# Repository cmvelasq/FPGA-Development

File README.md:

# QuickFeather Development Board 
- Features the PCB layout design updated with the EOS3FLF512-PDN64 BGA64 package
- Software tool : KiCad PCB Editor Ver 6.0.7  | https://www.kicad.org/
- Based on original PCB Design provided by Quicklogic | https://www.quicklogic.com/products/eos-s3/quickfeather-development-kit/

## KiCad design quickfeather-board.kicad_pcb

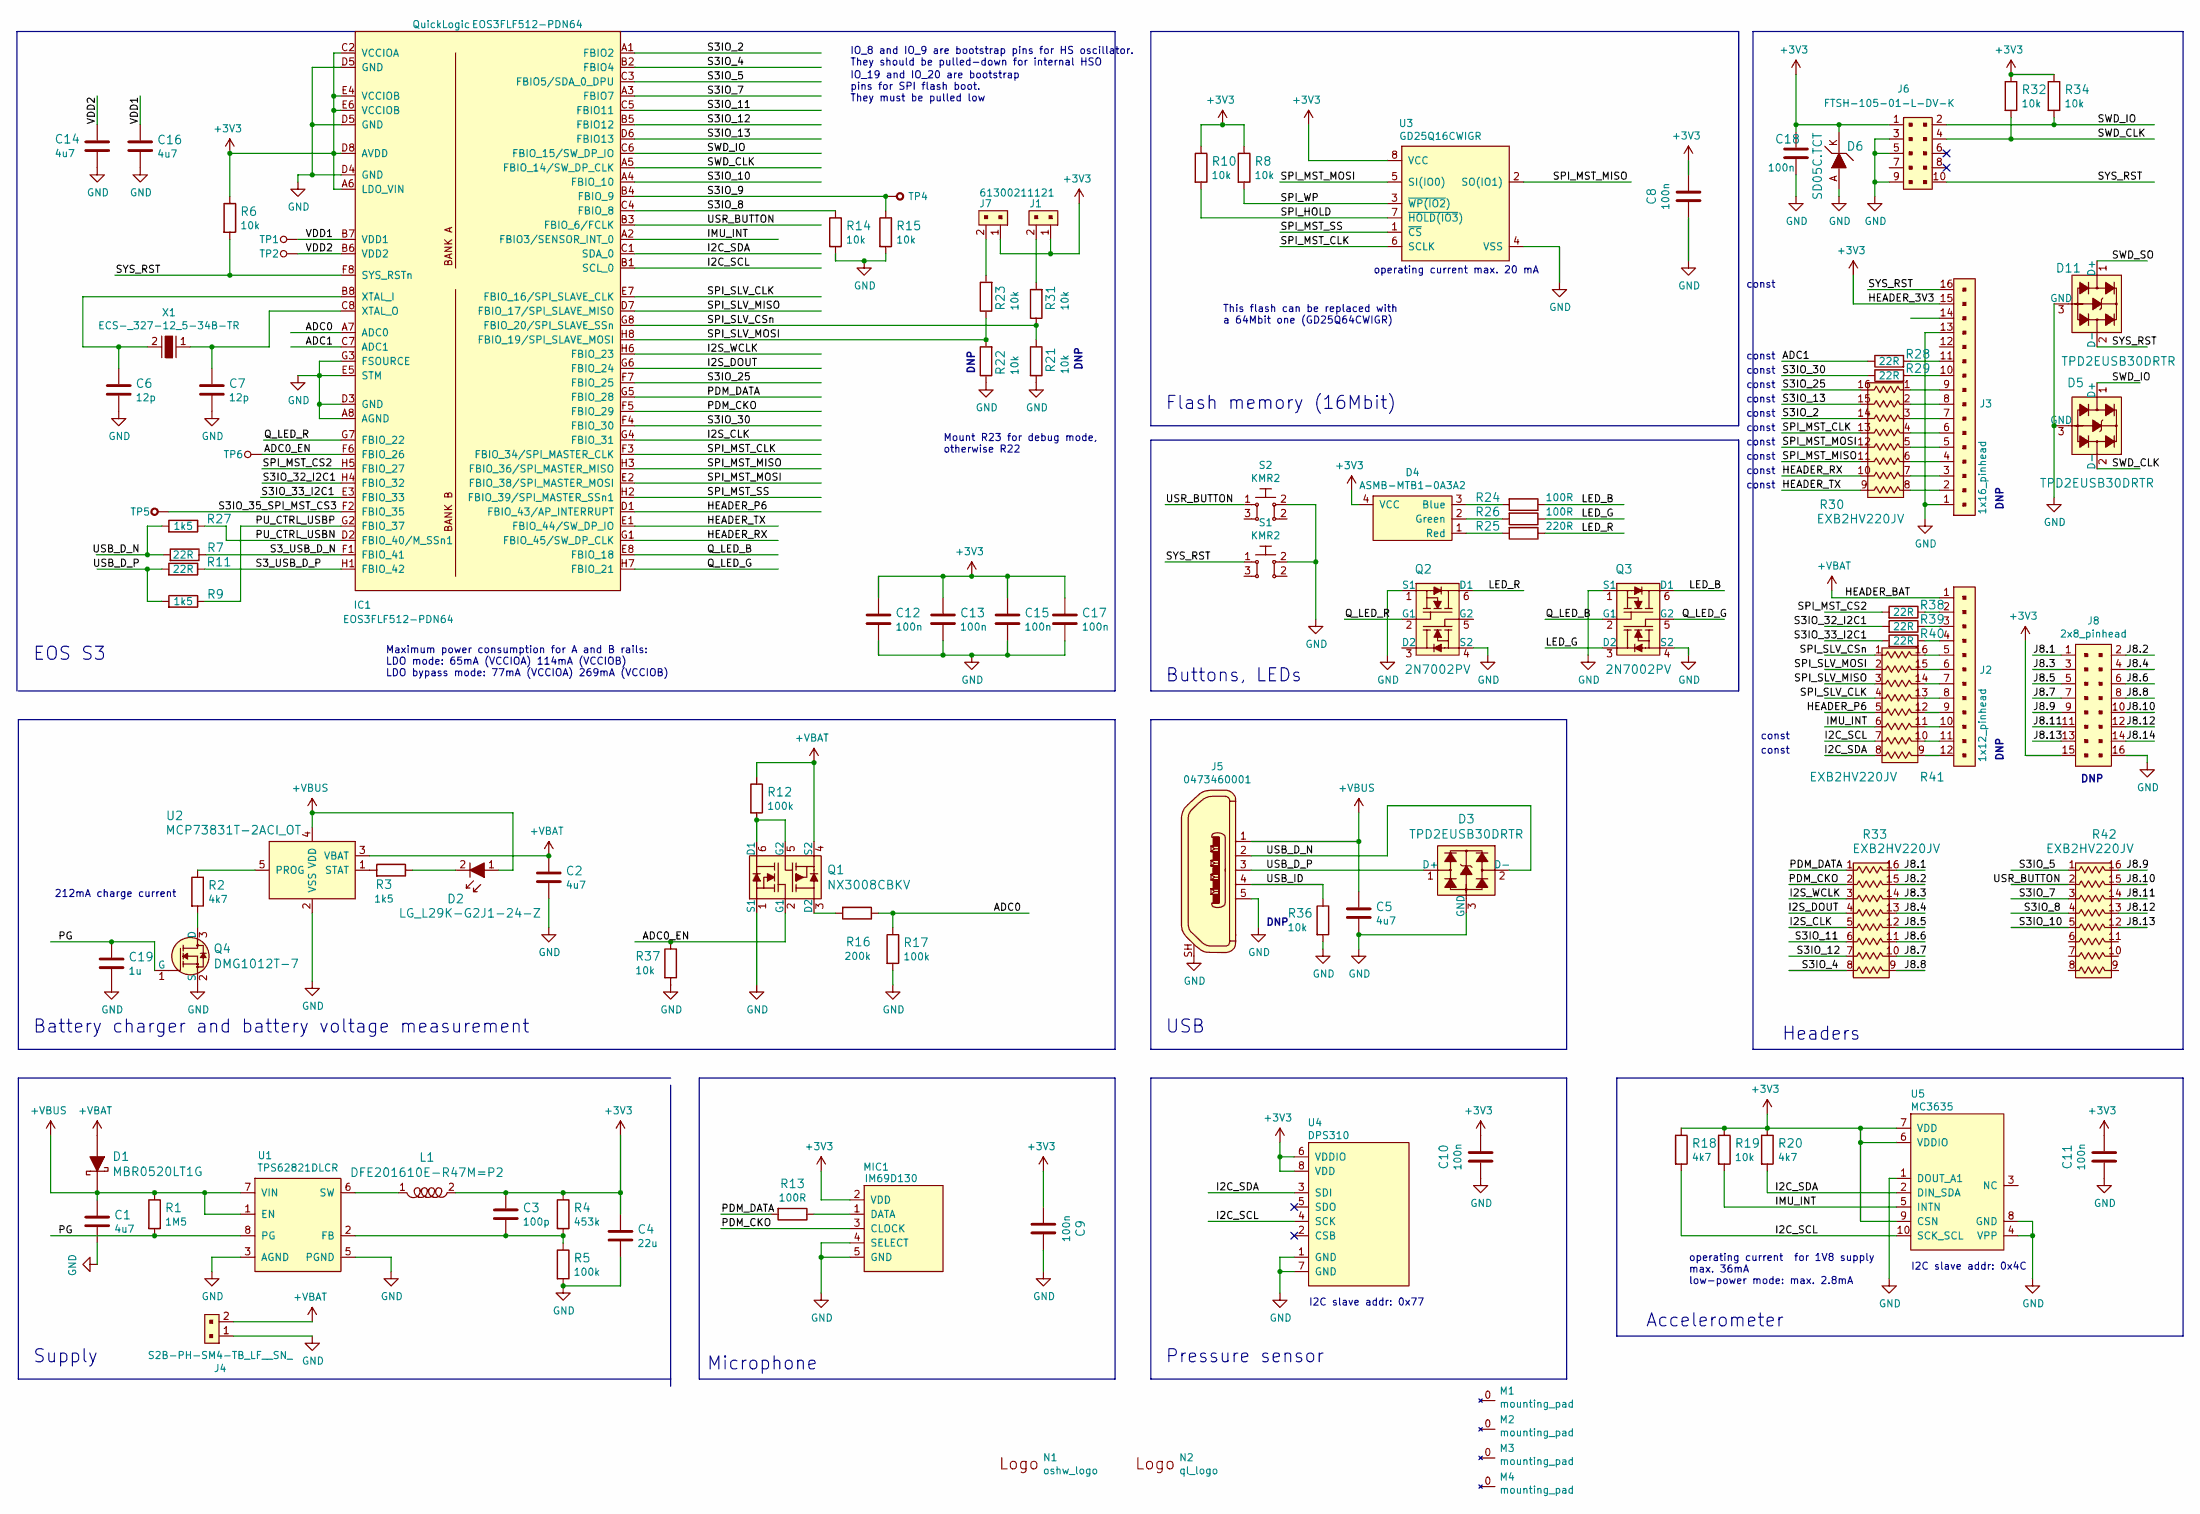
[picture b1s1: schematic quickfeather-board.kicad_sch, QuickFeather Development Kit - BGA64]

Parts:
C1, C2, C5, C14, C16: C_4u7_0603; 0603-cap; MPN C1608X5R1V475M080AC
C3: C_100p_0402; 0402-cap; MPN 0402N101J500CT
C4: C_22u_0603; 0603-cap; MPN GRM188R60J226MEA0D
C6, C7: C_12p_0402; 0402-cap; MPN CGA2B2C0G1H120J050BA
C8, C9, C10, C11, C12, C13, C15, C17, C18: C_100n_0402_6V3; 0402-cap; MPN 0402X104K6R3CT
C19: C_1u_0402; 0402-cap; MPN C1005X6S1A105K050BC
D1: MBR0520LT1G; SOD-123; MPN MBR0520LT1G
D2: LG_L29K-G2J1-24-Z; LED_0603; MPN LG L29K-G2J1-24-Z
D3, D5, D11: TPD2EUSB30DRTR; SOT-3; MPN TPD2EUSB30DRTR
D4: ASMB-MTB1-0A3A2; LED-PLCC4_3.2x2.8mm_B; MPN UHD1110-FKA
D6: SD05C.TCT; SOD-323-SD05; MPN SD05C.TCT
IC1: EOS3FLF512-PDN64; BGA-64_8x8_3.5x3.5mm; MPN EOS3FLF512-PDN64
J1, J7: 61300211121; PinHeader_1x2_P2.54_Drill0.9mm; MPN 61300211121
J2: 1x12_pinhead; MPN MC34733
J3: 1x16_pinhead; MPN 61301611121
J4: S2B-PH-SM4-TB_LF__SN_; PinHeader_2x1mm_P2mm_SMD_RA; MPN S2B-PH-SM4-TB(LF)(SN)
J5: 0473460001; USB_Micro_B_Female_0473460001; MPN 0473460001
J6: FTSH-105-01-L-DV-K; PinHeader_2x5_P1.27_SMD; MPN FTSH-105-01-L-DV-K
J8: 2x8_pinhead; MPN 2213S-16G
L1: DFE201610E-R47M=P2; 0806; MPN DFE201610E-R47M=P2
M1, M2, M3, M4: mounting_pad; MPAD
MIC1: IM69D130; MPN IM69D130
N1: oshw_logo; oshw-logo
N2: ql_logo; LOGO
Q1: NX3008CBKV; SOT-563; MPN NX3008CBKV
Q2, Q3: 2N7002PV; SOT-563; MPN 2N7002PV
Q4: DMG1012T-7; SOT-523; MPN DMG1012T-7
R1: R_1M5_0402; 0402-res; MPN MCWR04W1504FTL
R2, R18, R20: R_4k7_0402; 0402-res; MPN ERJ2GEJ472X
R3, R9, R27: R_1k5_0402; 0402-res; MPN ERJ2RKF1501X
R4: R_453k_0402; 0402-res; MPN CRCW0402453KFKED
R5, R12, R17: R_100k_0402; 0402-res; MPN CRCW0402100KFKEDHP
R6, R8, R10, R14, R15, R19, R21, R22, R23, R31, R32, R34, R36, R37: R_10k_0402; 0402-res; MPN CRCW040210K0FKEDHP
R7, R11, R28, R29, R38, R39, R40: R_22R_0402; 0402-res; MPN CRCW040222R0FKED
R13, R24, R26: R_100R_0402; 0402-res; MPN CR0402-FX-1000GLF
R16: R_200k_0402; 0402-res; MPN RC0402FR-07200KL
R25: R_220R_0402; 0402-res; MPN RMCF0402JT220R
R30, R33, R41, R42: EXB2HV220JV; R_Array_Convex_8x0602; MPN EXB2HV220JV
S1, S2: KMR2; SW_SPST_4.2x2.8; MPN KMR211NGLFS
TP1, TP2, TP6: TP_SMD1MM; Testpoint_smd_1mm; MPN N/A
TP4, TP5: TP_THT; Testpoint_THT_Drill0.9mm; MPN N/A
U1: TPS62821DLCR; QFN-8_2x1mm; MPN TPS62821DLCR
U2: MCP73831T-2ACI_OT; SOT-753; MPN MCP73831T-2ACI/OT
U3: GD25Q16CWIGR; GD25Q16CWIG; MPN GD25Q16CWIGR
U4: DPS310; PG-VLGA-8-2; MPN DPS310
U5: MC3635; MPN MC3635
X1: ECS-_327-12_5-34B-TR; SMD-2_3.2x1.5mm; MPN ECS-.327-12.5-34B-TR

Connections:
+3V3: C3.1, C4.1, C8.1, C9.2, C10.1, C11.1, C12.1, C13.1, C15.1, C17.1, C18.1, D4.4 (VCC), D6.K, IC1.A6 (LDO_VIN), IC1.C2 (VCCIOA), IC1.D8 (AVDD), IC1.E4 (VCCIOB), IC1.E6 (VCCIOB), J1.1, J3.15, J6.1, J7.1, J8.15, L1.2, MIC1.2 (VDD), R4.1, R6.1, R8.1, R10.1, R18.1, R19.1, R20.1, R32.1, R34.1, U3.8 (VCC), U4.6 (VDDIO), U4.8 (VDD), U5.6 (VDDIO), U5.7 (VDD), U5.9 (CSN)
+VBAT: C2.1, D1.A, J2.1, J4.2, Q1.4 (S2), R12.1, U2.3 (VBAT)
+VBUS: C1.1, C5.1, D1.K, D2.1, J5.1, R1.1, U1.1 (EN), U1.7 (VIN), U2.4 (VDD)
/ADC0: IC1.A7 (ADC0), R16.1, R17.1
/ADC0_EN: IC1.F6 (FBIO_26), Q1.2 (G1), R37.1, TP6.1
/ADC1: IC1.C7 (ADC1), R28.1
/HEADER_P6: IC1.D1 (FBIO_43/AP_INTERRUPT), R41.5
/HEADER_RX: IC1.G1 (FBIO_45/SW_DP_CLK), R30.10
/HEADER_TX: IC1.E1 (FBIO_44/SW_DP_IO), R30.9
/I2C_SCL: IC1.B1 (SCL_0), R18.2, R41.7, U4.4 (SCK), U5.10 (SCK_SCL)
/I2C_SDA: IC1.C1 (SDA_0), R20.2, R41.8, U4.3 (SDI), U5.2 (DIN_SDA)
/I2S_CLK: IC1.G4 (FBIO_31), R33.5
/I2S_DOUT: IC1.G6 (FBIO_24), R33.4
/I2S_WCLK: IC1.H6 (FBIO_23), R33.3
/IMU_INT: IC1.A2 (FBIO3/SENSOR_INT_0), R19.2, R41.6, U5.5 (INTN)
/J8.1: J8.1, R33.16
/J8.2: J8.2, R33.15
/J8.3: J8.3, R33.14
/J8.4: J8.4, R33.13
/J8.5: J8.5, R33.12
/J8.6: J8.6, R33.11
/J8.7: J8.7, R33.10
/J8.8: J8.8, R33.9
/J8.9: J8.9, R42.16
/J8.10: J8.10, R42.15
/J8.11: J8.11, R42.14
/J8.12: J8.12, R42.13
/J8.13: J8.13, R42.12
/J8.14: J8.14
/LED_B: Q3.6 (D1), R24.1
/LED_G: Q3.3 (D2), R26.1
/LED_R: Q2.6 (D1), R25.1
/PDM_CKO: IC1.F5 (FBIO_29), MIC1.3 (CLOCK), R33.2
/PDM_DATA: IC1.G5 (FBIO_28), R13.2, R33.1
/PG: C19.1, Q4.1 (G), R1.2, U1.8 (PG)
/PU_CTRL_USBN: IC1.D2 (FBIO_40/M_SSn1), R27.1
/PU_CTRL_USBP: IC1.G2 (FBIO_37), R9.1
/Q_LED_B: IC1.E8 (FBIO_18), Q3.2 (G1)
/Q_LED_G: IC1.H7 (FBIO_21), Q3.5 (G2)
/Q_LED_R: IC1.G7 (FBIO_22), Q2.2 (G1)
/S3IO_2: IC1.A1 (FBIO2), R30.14
/S3IO_4: IC1.B2 (FBIO4), R33.8
/S3IO_5: IC1.C3 (FBIO5/SDA_0_DPU), R42.1
/S3IO_7: IC1.A3 (FBIO7), R42.3
/S3IO_8: IC1.C4 (FBIO_8), R14.1, R42.4
/S3IO_9: IC1.B4 (FBIO_9), R15.1, TP4.1
/S3IO_10: IC1.A4 (FBIO_10), R42.5
/S3IO_11: IC1.C5 (FBIO11), R33.6
/S3IO_12: IC1.B5 (FBIO12), R33.7
/S3IO_13: IC1.D6 (FBIO13), R30.15
/S3IO_25: IC1.F7 (FBIO_25), R30.16
/S3IO_30: IC1.F4 (FBIO_30), R29.1
/S3IO_32_I2C1: IC1.H4 (FBIO_32), R39.2
/S3IO_33_I2C1: IC1.E3 (FBIO_33), R40.2
/S3IO_35_SPI_MST_CS3: IC1.F2 (FBIO_35), TP5.1
/S3_USB_D_N: IC1.F1 (FBIO_41), R7.1
/S3_USB_D_P: IC1.H1 (FBIO_42), R11.1
/SPI_HOLD: R10.2, U3.7 (~HOLD(IO3))
/SPI_MST_CLK: IC1.F3 (FBIO_34/SPI_MASTER_CLK), R30.13, U3.6 (SCLK)
/SPI_MST_CS2: IC1.H5 (FBIO_27), R38.2
/SPI_MST_MISO: IC1.H3 (FBIO_36/SPI_MASTER_MISO), R30.11, U3.2 (SO(IO1))
/SPI_MST_MOSI: IC1.E2 (FBIO_38/SPI_MASTER_MOSI), R30.12, U3.5 (SI(IO0))
/SPI_MST_SS: IC1.H2 (FBIO_39/SPI_MASTER_SSn1), U3.1 (~CS)
/SPI_SLV_CLK: IC1.E7 (FBIO_16/SPI_SLAVE_CLK), R41.4
/SPI_SLV_CSn: IC1.G8 (FBIO_20/SPI_SLAVE_SSn), R21.1, R31.1, R41.1
/SPI_SLV_MISO: IC1.D7 (FBIO_17/SPI_SLAVE_MISO), R41.3
/SPI_SLV_MOSI: IC1.H8 (FBIO_19/SPI_SLAVE_MOSI), R22.2, R23.1, R41.2
/SPI_WP: R8.2, U3.3 (~WP(IO2))
/SWD_CLK: D5.2 (D-), IC1.A5 (FBIO_14/SW_DP_CLK), J6.4, R32.2
/SWD_IO: D5.1 (D+), IC1.C6 (FBIO_15/SW_DP_IO), J6.2, R34.2
/SWD_SO: D11.1 (D+)
/SYS_RST: D11.2 (D-), IC1.F8 (SYS_RSTn), J3.16, J6.10, R6.2, S1.1
/USB_D_N: D3.2 (D-), J5.2, R7.2, R27.2
/USB_D_P: D3.1 (D+), J5.3, R9.2, R11.2
/USB_ID: J5.4, R36.1
/USR_BUTTON: IC1.B3 (FBIO_6/FCLK), R42.2, S2.1
/VDD1: C16.1, IC1.B7 (VDD1), TP1.1
/VDD2: C14.1, IC1.B6 (VDD2), TP2.1
GND: C1.2, C2.2, C4.2, C5.2, C6.2, C7.2, C8.2, C9.1, C10.2, C11.2, C12.2, C13.2, C14.2, C15.2, C16.2, C17.2, C18.2, C19.2, D3.3 (GND), D5.3 (GND), D6.A, D11.3 (GND), IC1.A8 (AGND), IC1.D3 (GND), IC1.D4 (GND), IC1.D5 (GND), IC1.E5 (STM), IC1.G3 (FSOURCE), J3.1, J3.13, J4.1, J5.5, J5.SH, J6.3, J6.5, J6.9, J8.16, MIC1.4 (SELECT), MIC1.5 (GND), Q1.1 (S1), Q2.1 (S1), Q2.4 (S2), Q3.1 (S1), Q3.4 (S2), Q4.2 (S), R5.2, R14.2, R15.2, R17.2, R21.2, R22.1, R36.2, R37.2, S1.2, S2.2, U1.3 (AGND), U1.5 (PGND), U2.2 (VSS), U3.4 (VSS), U4.1 (GND), U4.7 (GND), U5.1 (DOUT_A1), U5.4 (VPP), U5.8 (GND)
unnamed: C3.2, R4.2, R5.1, U1.2 (FB)
unnamed: C6.1, IC1.B8 (XTAL_I), X1.2
unnamed: C7.1, IC1.C8 (XTAL_O), X1.1
unnamed: D2.2, R3.1
unnamed: D4.1 (Red), R25.2
unnamed: D4.2 (Green), R26.2
unnamed: D4.3 (Blue), R24.2
unnamed: J1.2, R31.2
unnamed: J2.2, R38.1
unnamed: J2.3, R39.1
unnamed: J2.4, R40.1
unnamed: J2.5, R41.16
unnamed: J2.6, R41.15
unnamed: J2.7, R41.14
unnamed: J2.8, R41.13
unnamed: J2.9, R41.12
unnamed: J2.10, R41.11
unnamed: J2.11, R41.10
unnamed: J2.12, R41.9
unnamed: J3.2, R30.8
unnamed: J3.3, R30.7
unnamed: J3.4, R30.6
unnamed: J3.5, R30.5
unnamed: J3.6, R30.4
unnamed: J3.7, R30.3
unnamed: J3.8, R30.2
unnamed: J3.9, R30.1
unnamed: J3.10, R29.2
unnamed: J3.11, R28.2
unnamed: J7.2, R23.2
unnamed: L1.1, U1.6 (SW)
unnamed: MIC1.1 (DATA), R13.1
unnamed: Q1.3 (D2), R16.2
unnamed: Q1.5 (G2), Q1.6 (D1), R12.2
unnamed: Q4.3 (D), R2.2
unnamed: R2.1, U2.5 (PROG)
unnamed: R3.2, U2.1 (STAT)

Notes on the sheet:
const
operating current max. 20 mA
DNP
I2C slave addr: 0x77
IO_19 and IO_20 are bootstrap pins for SPI flash boot. They must be pulled low
Buttons, LEDs
Microphone
Flash memory (16Mbit)
Accelerometer
IO_8 and IO_9 are bootstrap pins for HS oscillator. They should be pulled-down for internal HSO
Battery charger and battery voltage measurement
Maximum power consumption for A and B rails: LDO mode: 65mA (VCCIOA) 114mA (VCCIOB) LDO bypass mode: 77mA (VCCIOA) 269mA (VCCIOB)
212mA charge current
This flash can be replaced with a 64Mbit one (GD25Q64CWIGR)
Pressure sensor
Mount R23 for debug mode, otherwise R22
Supply
EOS S3
operating current for 1V8 supply max. 36mA low-power mode: max. 2.8mA
Headers
USB
I2C slave addr: 0x4C

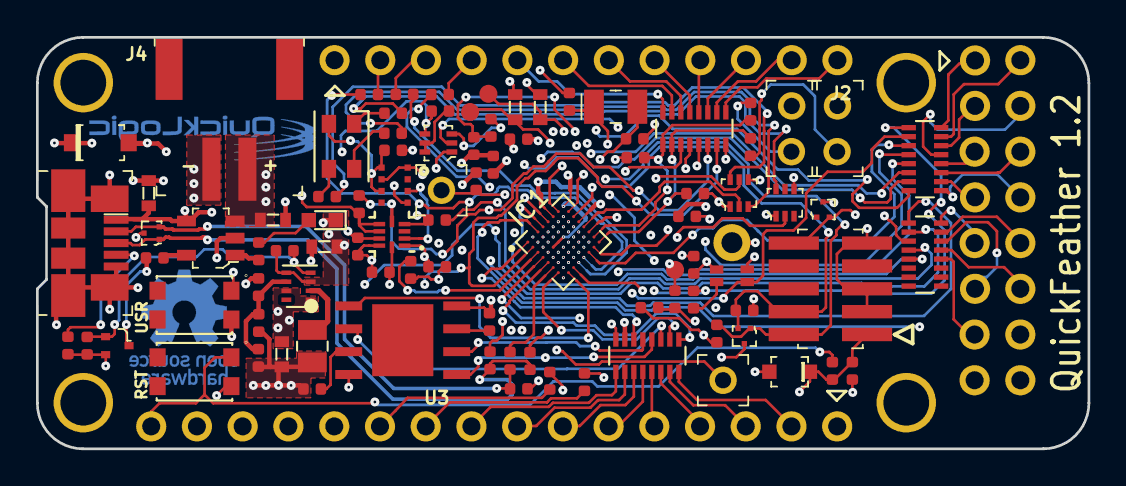
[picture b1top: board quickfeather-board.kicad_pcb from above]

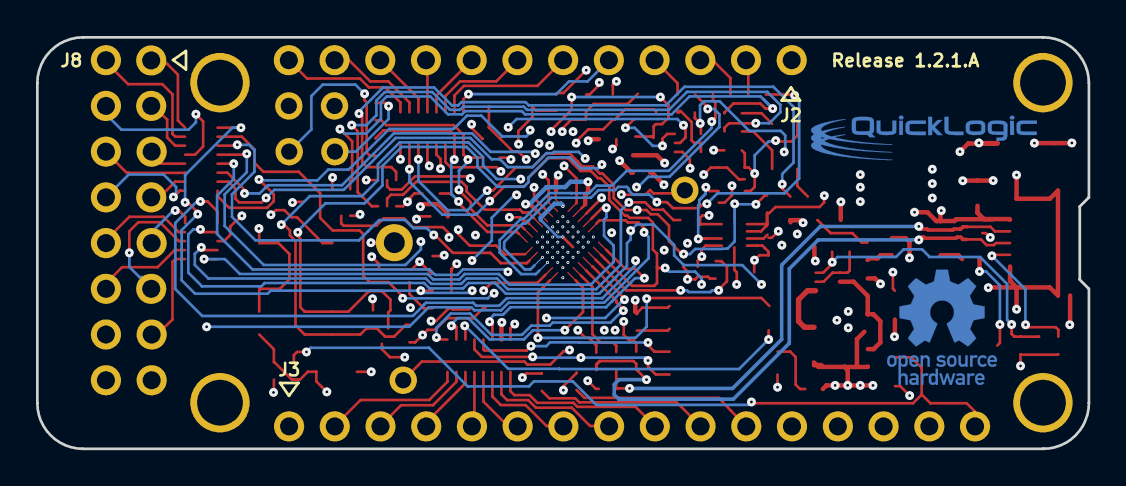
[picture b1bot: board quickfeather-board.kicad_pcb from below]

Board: 4 copper layers, 58.4 x 22.9 mm, 101 parts (2 on the bottom side), 114 nets.
